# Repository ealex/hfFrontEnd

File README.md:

# hfFrontEnd
Receiver front end, to go along with https://github.com/ealex/hfBandPassFilterBlock

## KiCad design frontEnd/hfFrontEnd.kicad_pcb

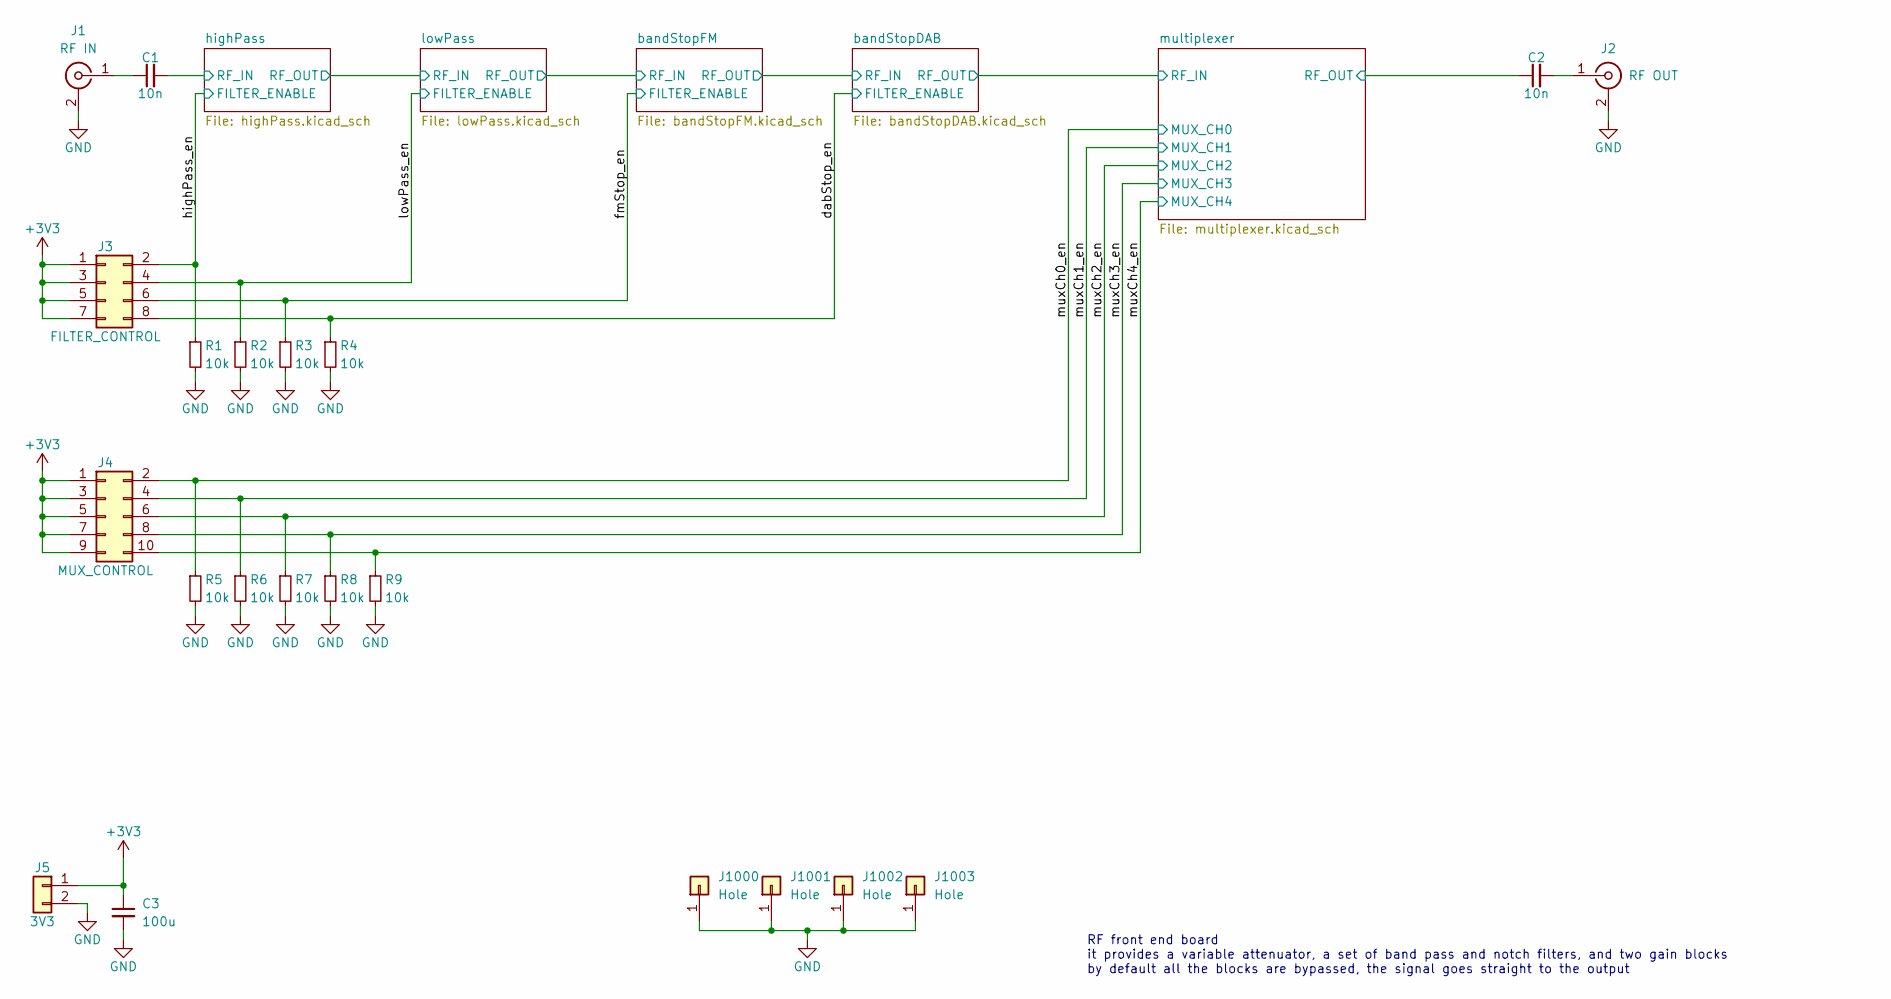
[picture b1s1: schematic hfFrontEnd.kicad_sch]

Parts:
C1, C2: 10n; C_0805_2012Metric
C3: 100u; CP_Radial_D5.0mm_P2.50mm
J1: RF IN; SMA
J2: RF OUT; SMA
J3: FILTER_CONTROL; PinHeader_2x04_P2.54mm_Vertical
J4: MUX_CONTROL; PinHeader_2x05_P2.54mm_Vertical
J5: 3V3; PinHeader_1x02_P2.54mm_Vertical
J1000, J1001, J1002, J1003: Hole; MountingHole_3.2mm_M3_DIN965_Pad
R1, R2, R3, R4, R5, R6, R7, R8, R9: 10k; R_0805_2012Metric

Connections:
+3V3: C3.1, J3.1, J3.3, J3.5, J3.7, J4.1, J4.3, J4.5, J4.7, J4.9, J5.1; also elsewhere on the board
/dabStop_en: J3.8, R4.1; also elsewhere on the board
/fmStop_en: J3.6, R3.1; also elsewhere on the board
/highPass/RF_IN: C1.2; also elsewhere on the board
/highPass_en: J3.2, R1.1; also elsewhere on the board
/lowPass_en: J3.4, R2.1; also elsewhere on the board
/multiplexer/RF_OUT: C2.1; also elsewhere on the board
/muxCh0_en: J4.2, R5.1; also elsewhere on the board
/muxCh1_en: J4.4, R6.1; also elsewhere on the board
/muxCh2_en: J4.6, R7.1; also elsewhere on the board
/muxCh3_en: J4.8, R8.1; also elsewhere on the board
/muxCh4_en: J4.10, R9.1; also elsewhere on the board
GND: C3.2, J1.2 (Ext), J2.2 (Ext), J5.2, J1000.1, J1001.1, J1002.1, J1003.1, R1.2, R2.2, R3.2, R4.2, R5.2, R6.2, R7.2, R8.2, R9.2; also elsewhere on the board
unnamed: C1.1, J1.1 (In)
unnamed: C2.2, J2.1 (In)

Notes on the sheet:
RF front end board it provides a variable attenuator, a set of band pass and notch filters, and two gain blocks by default all the blocks are bypassed, the signal goes straight to the output

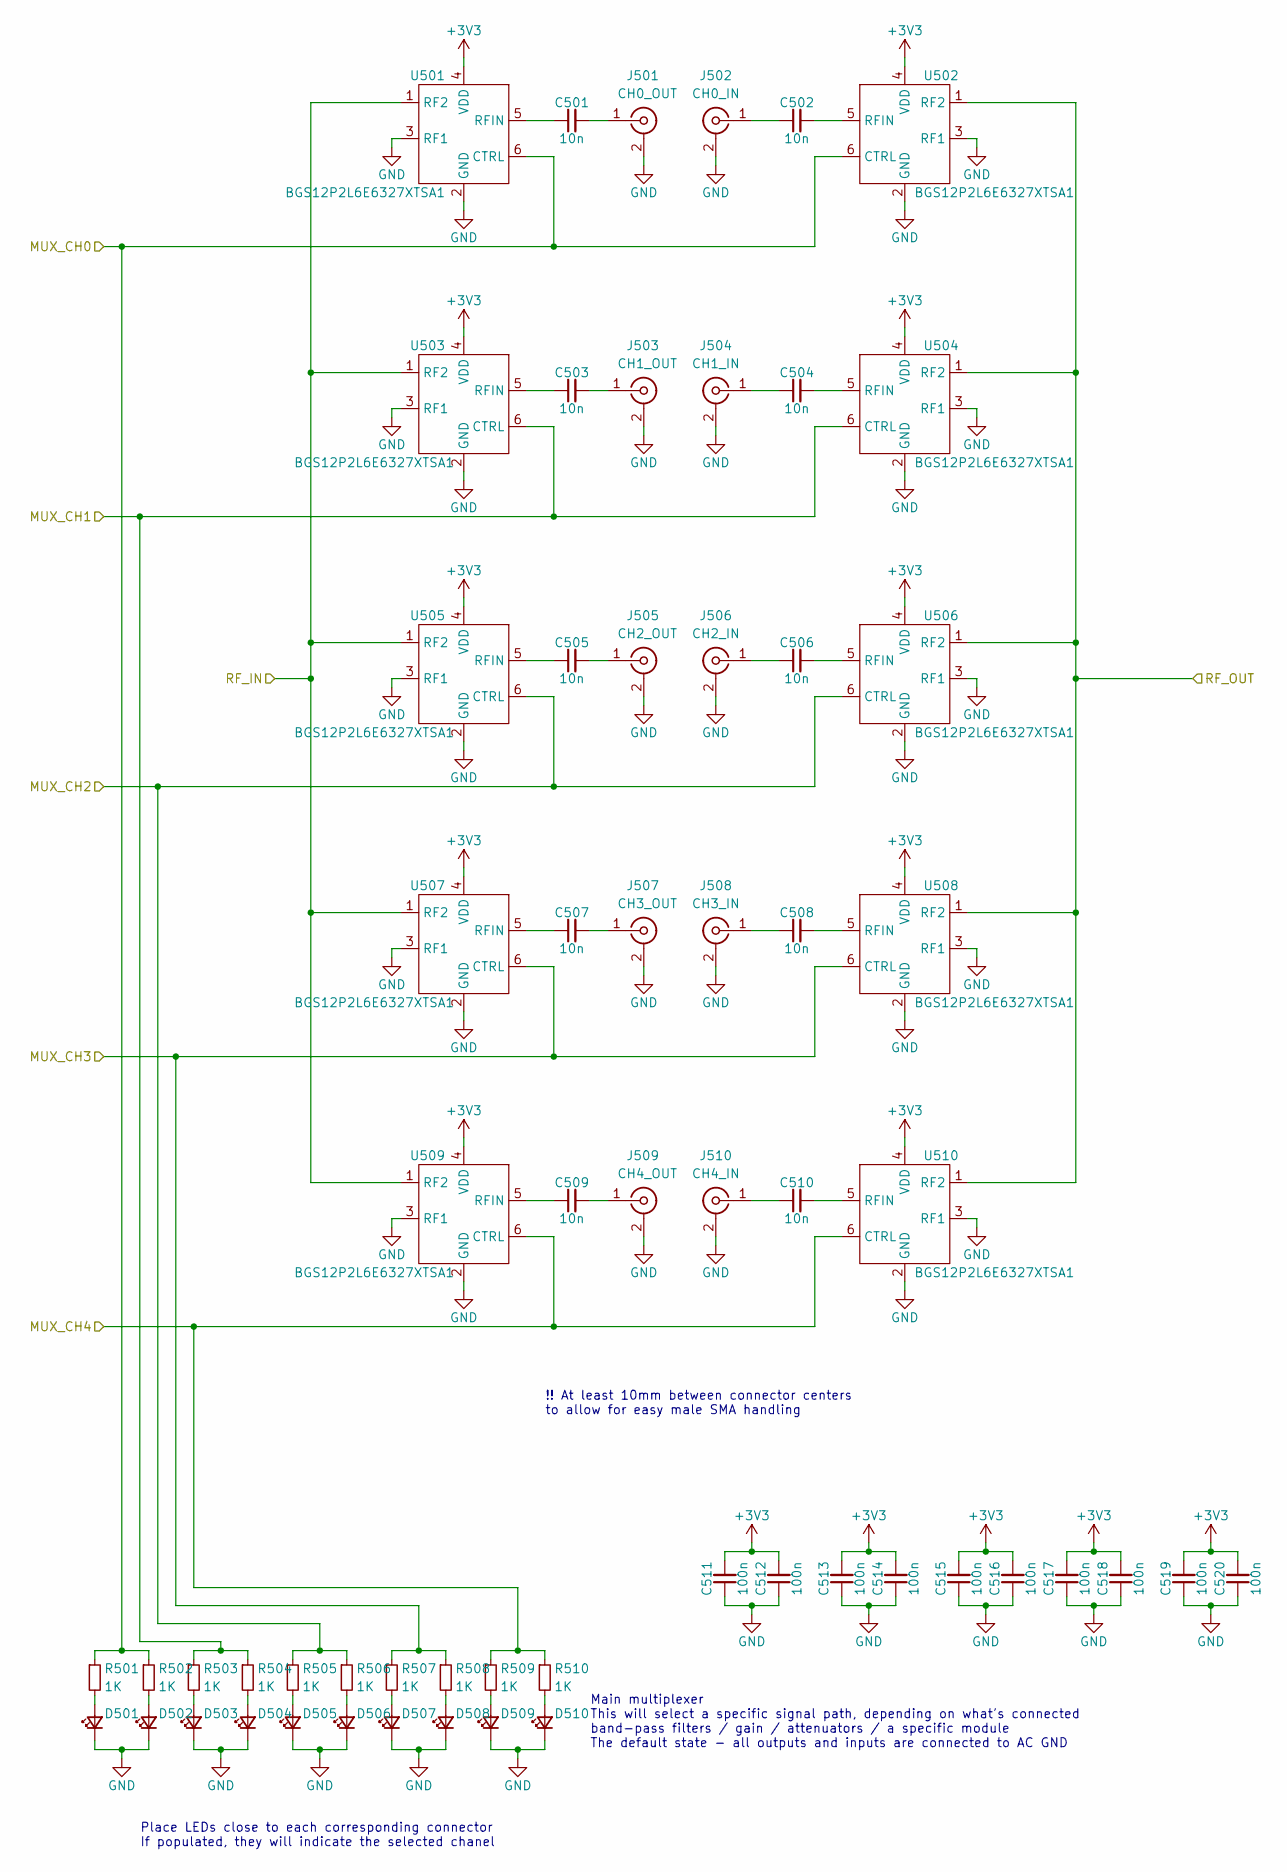
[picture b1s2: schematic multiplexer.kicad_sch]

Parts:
C501, C502, C503, C504, C505, C506, C507, C508, C509, C510: 10n; C_0805_2012Metric
C511, C512, C513, C514, C515, C516, C517, C518, C519, C520: 100n; C_0805_2012Metric
D501, D502, D503, D504, D505, D506, D507, D508, D509, D510: LED_Small; LED_0805_2012Metric
J501: CH0_OUT; SMA_FEM_TH_VERTICAL
J502: CH0_IN; SMA_FEM_TH_VERTICAL
J503: CH1_OUT; SMA_FEM_TH_VERTICAL
J504: CH1_IN; SMA_FEM_TH_VERTICAL
J505: CH2_OUT; SMA_FEM_TH_VERTICAL
J506: CH2_IN; SMA_FEM_TH_VERTICAL
J507: CH3_OUT; SMA_FEM_TH_VERTICAL
J508: CH3_IN; SMA_FEM_TH_VERTICAL
J509: CH4_OUT; SMA_FEM_TH_VERTICAL
J510: CH4_IN; SMA_FEM_TH_VERTICAL
R501, R502, R503, R504, R505, R506, R507, R508, R509, R510: 1K; R_0805_2012Metric
U501, U502, U503, U504, U505, U506, U507, U508, U509, U510: BGS12P2L6E6327XTSA1

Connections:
+3V3: C511.2, C512.2, C513.2, C514.2, C515.2, C516.2, C517.2, C518.2, C519.2, C520.2, U501.4 (VDD), U502.4 (VDD), U503.4 (VDD), U504.4 (VDD), U505.4 (VDD), U506.4 (VDD), U507.4 (VDD), U508.4 (VDD), U509.4 (VDD), U510.4 (VDD); also elsewhere on the board
/bandStopDAB/RF_OUT: U501.1 (RF2), U503.1 (RF2), U505.1 (RF2), U507.1 (RF2), U509.1 (RF2); also elsewhere on the board
/multiplexer/RF_OUT: U502.1 (RF2), U504.1 (RF2), U506.1 (RF2), U508.1 (RF2), U510.1 (RF2); also elsewhere on the board
/muxCh0_en: R501.1, R502.1, U501.6 (CTRL), U502.6 (CTRL); also elsewhere on the board
/muxCh1_en: R503.1, R504.1, U503.6 (CTRL), U504.6 (CTRL); also elsewhere on the board
/muxCh2_en: R505.1, R506.1, U505.6 (CTRL), U506.6 (CTRL); also elsewhere on the board
/muxCh3_en: R507.1, R508.1, U507.6 (CTRL), U508.6 (CTRL); also elsewhere on the board
/muxCh4_en: R509.1, R510.1, U509.6 (CTRL), U510.6 (CTRL); also elsewhere on the board
GND: C511.1, C512.1, C513.1, C514.1, C515.1, C516.1, C517.1, C518.1, C519.1, C520.1, D501.1 (K), D502.1 (K), D503.1 (K), D504.1 (K), D505.1 (K), D506.1 (K), D507.1 (K), D508.1 (K), D509.1 (K), D510.1 (K), J501.2 (Ext), J502.2 (Ext), J503.2 (Ext), J504.2 (Ext), J505.2 (Ext), J506.2 (Ext), J507.2 (Ext), J508.2 (Ext), J509.2 (Ext), J510.2 (Ext), U501.2 (GND), U501.3 (RF1), U502.2 (GND), U502.3 (RF1), U503.2 (GND), U503.3 (RF1), U504.2 (GND), U504.3 (RF1), U505.2 (GND), U505.3 (RF1), U506.2 (GND), U506.3 (RF1), U507.2 (GND), U507.3 (RF1), U508.2 (GND), U508.3 (RF1), U509.2 (GND), U509.3 (RF1), U510.2 (GND), U510.3 (RF1); also elsewhere on the board
unnamed: C501.1, U501.5 (RFIN)
unnamed: C501.2, J501.1 (In)
unnamed: C502.1, J502.1 (In)
unnamed: C502.2, U502.5 (RFIN)
unnamed: C503.1, U503.5 (RFIN)
unnamed: C503.2, J503.1 (In)
unnamed: C504.1, J504.1 (In)
unnamed: C504.2, U504.5 (RFIN)
unnamed: C505.1, U505.5 (RFIN)
unnamed: C505.2, J505.1 (In)
unnamed: C506.1, J506.1 (In)
unnamed: C506.2, U506.5 (RFIN)
unnamed: C507.1, U507.5 (RFIN)
unnamed: C507.2, J507.1 (In)
unnamed: C508.1, J508.1 (In)
unnamed: C508.2, U508.5 (RFIN)
unnamed: C509.1, U509.5 (RFIN)
unnamed: C509.2, J509.1 (In)
unnamed: C510.1, J510.1 (In)
unnamed: C510.2, U510.5 (RFIN)
unnamed: D501.2 (A), R501.2
unnamed: D502.2 (A), R502.2
unnamed: D503.2 (A), R503.2
unnamed: D504.2 (A), R504.2
unnamed: D505.2 (A), R505.2
unnamed: D506.2 (A), R506.2
unnamed: D507.2 (A), R507.2
unnamed: D508.2 (A), R508.2
unnamed: D509.2 (A), R509.2
unnamed: D510.2 (A), R510.2

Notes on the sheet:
!! At least 10mm between connector centers to allow for easy male SMA handling
Place LEDs close to each corresponding connector If populated, they will indicate the selected chanel
Main multiplexer This will select a specific signal path, depending on what's connected band-pass filters / gain / attenuators / a specific module The default state - all outputs and inputs are connected to AC GND

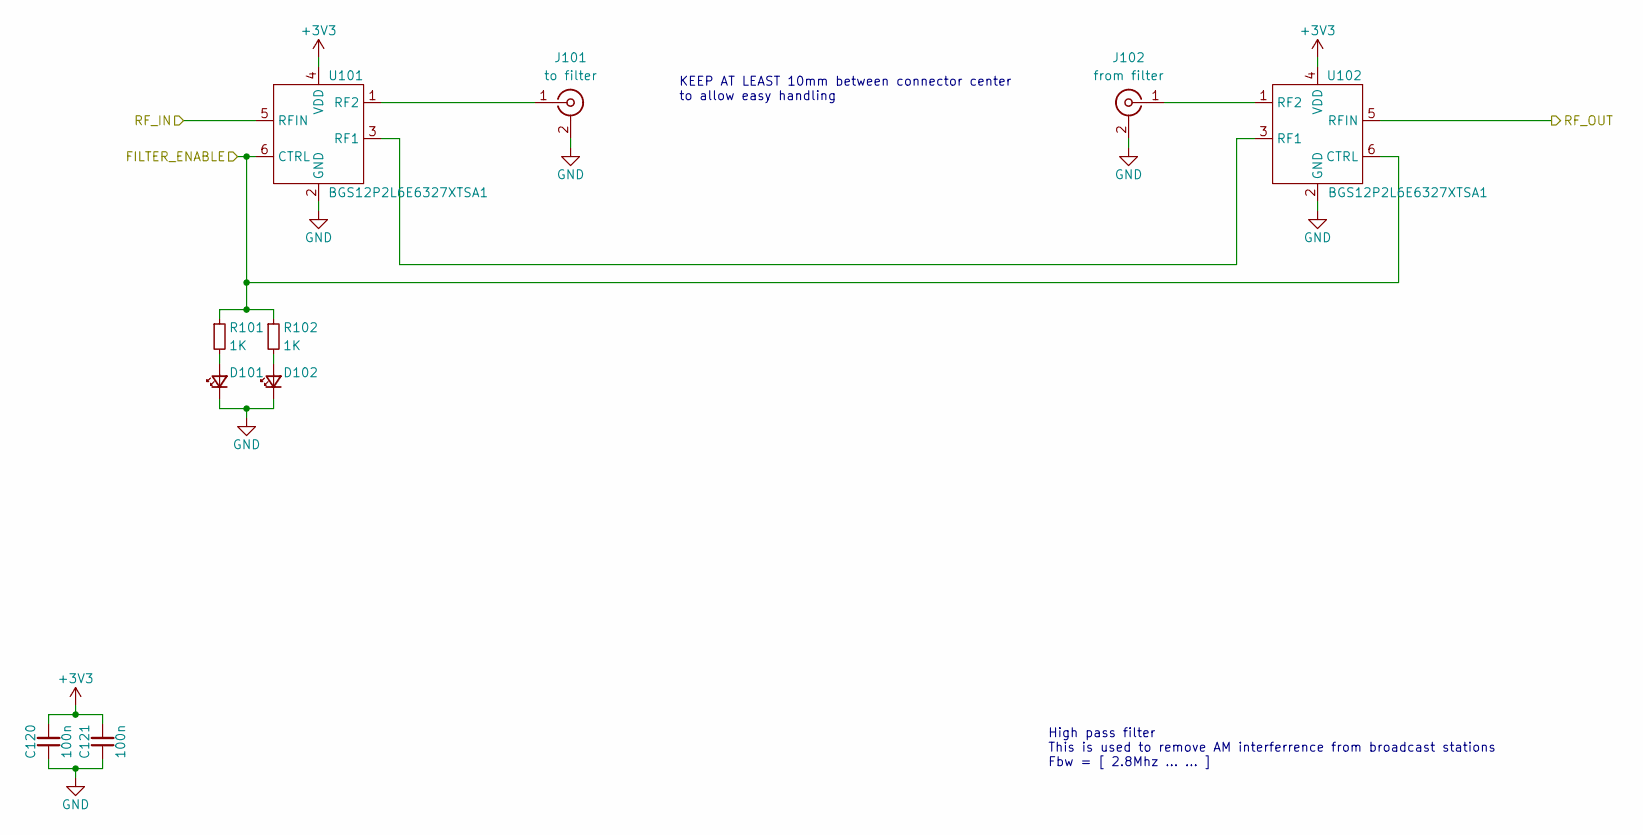
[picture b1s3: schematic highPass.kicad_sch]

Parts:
C120, C121: 100n; C_0805_2012Metric
D101, D102: LED_Small; LED_0805_2012Metric
J101: to filter; SMA_FEM_TH_VERTICAL
J102: from filter; SMA_FEM_TH_VERTICAL
R101, R102: 1K; R_0805_2012Metric
U101, U102: BGS12P2L6E6327XTSA1

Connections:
+3V3: C120.2, C121.2, U101.4 (VDD), U102.4 (VDD); also elsewhere on the board
/highPass/RF_IN: U101.5 (RFIN); also elsewhere on the board
/highPass/RF_OUT: U102.5 (RFIN); also elsewhere on the board
/highPass_en: R101.1, R102.1, U101.6 (CTRL), U102.6 (CTRL); also elsewhere on the board
GND: C120.1, C121.1, D101.1 (K), D102.1 (K), J101.2 (Ext), J102.2 (Ext), U101.2 (GND), U102.2 (GND); also elsewhere on the board
unnamed: D101.2 (A), R101.2
unnamed: D102.2 (A), R102.2
unnamed: J101.1 (In), U101.1 (RF2)
unnamed: J102.1 (In), U102.1 (RF2)
unnamed: U101.3 (RF1), U102.3 (RF1)

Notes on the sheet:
KEEP AT LEAST 10mm between connector center to allow easy handling
High pass filter This is used to remove AM interferrence from broadcast stations Fbw = [ 2.8Mhz ... ... ]

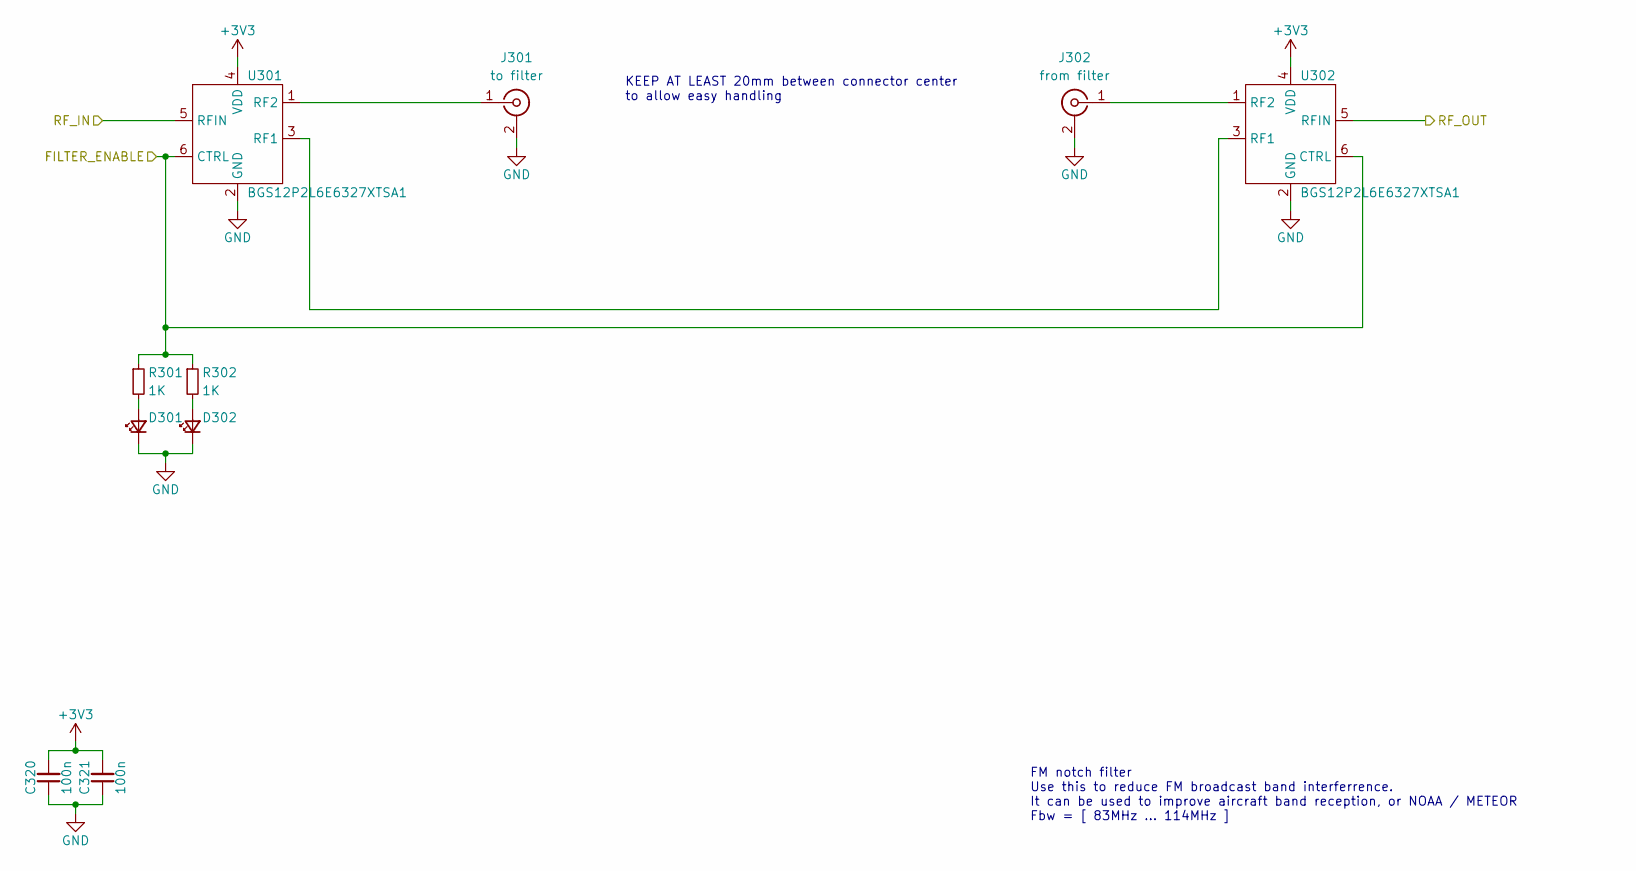
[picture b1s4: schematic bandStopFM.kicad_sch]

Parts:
C320, C321: 100n; C_0805_2012Metric
D301, D302: LED_Small; LED_0805_2012Metric
J301: to filter; SMA_FEM_TH_VERTICAL
J302: from filter; SMA_FEM_TH_VERTICAL
R301, R302: 1K; R_0805_2012Metric
U301, U302: BGS12P2L6E6327XTSA1

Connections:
+3V3: C320.2, C321.2, U301.4 (VDD), U302.4 (VDD); also elsewhere on the board
/bandStopDAB/RF_IN: U302.5 (RFIN); also elsewhere on the board
/bandStopFM/RF_IN: U301.5 (RFIN); also elsewhere on the board
/fmStop_en: R301.1, R302.1, U301.6 (CTRL), U302.6 (CTRL); also elsewhere on the board
GND: C320.1, C321.1, D301.1 (K), D302.1 (K), J301.2 (Ext), J302.2 (Ext), U301.2 (GND), U302.2 (GND); also elsewhere on the board
unnamed: D301.2 (A), R301.2
unnamed: D302.2 (A), R302.2
unnamed: J301.1 (In), U301.1 (RF2)
unnamed: J302.1 (In), U302.1 (RF2)
unnamed: U301.3 (RF1), U302.3 (RF1)

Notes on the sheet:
FM notch filter Use this to reduce FM broadcast band interferrence. It can be used to improve aircraft band reception, or NOAA / METEOR Fbw = [ 83MHz ... 114MHz ]
KEEP AT LEAST 20mm between connector center to allow easy handling

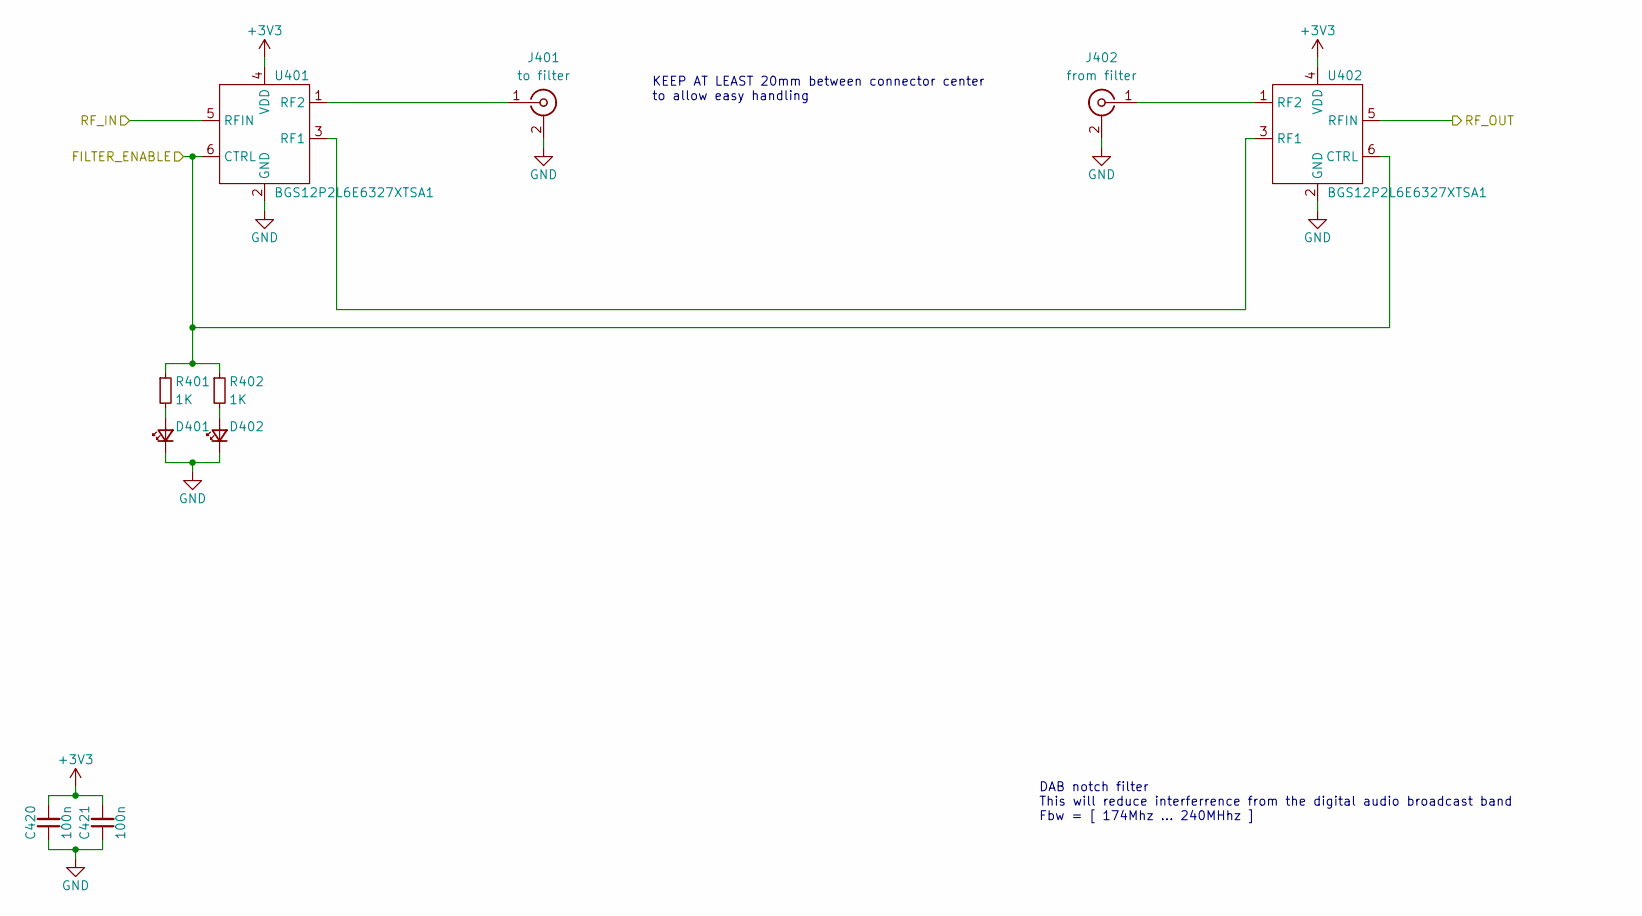
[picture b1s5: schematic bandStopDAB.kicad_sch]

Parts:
C420, C421: 100n; C_0805_2012Metric
D401, D402: LED_Small; LED_0805_2012Metric
J401: to filter; SMA_FEM_TH_VERTICAL
J402: from filter; SMA_FEM_TH_VERTICAL
R401, R402: 1K; R_0805_2012Metric
U401, U402: BGS12P2L6E6327XTSA1

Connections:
+3V3: C420.2, C421.2, U401.4 (VDD), U402.4 (VDD); also elsewhere on the board
/bandStopDAB/RF_IN: U401.5 (RFIN); also elsewhere on the board
/bandStopDAB/RF_OUT: U402.5 (RFIN); also elsewhere on the board
/dabStop_en: R401.1, R402.1, U401.6 (CTRL), U402.6 (CTRL); also elsewhere on the board
GND: C420.1, C421.1, D401.1 (K), D402.1 (K), J401.2 (Ext), J402.2 (Ext), U401.2 (GND), U402.2 (GND); also elsewhere on the board
unnamed: D401.2 (A), R401.2
unnamed: D402.2 (A), R402.2
unnamed: J401.1 (In), U401.1 (RF2)
unnamed: J402.1 (In), U402.1 (RF2)
unnamed: U401.3 (RF1), U402.3 (RF1)

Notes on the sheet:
DAB notch filter This will reduce interferrence from the digital audio broadcast band Fbw = [ 174Mhz ... 240MHhz ]
KEEP AT LEAST 20mm between connector center to allow easy handling

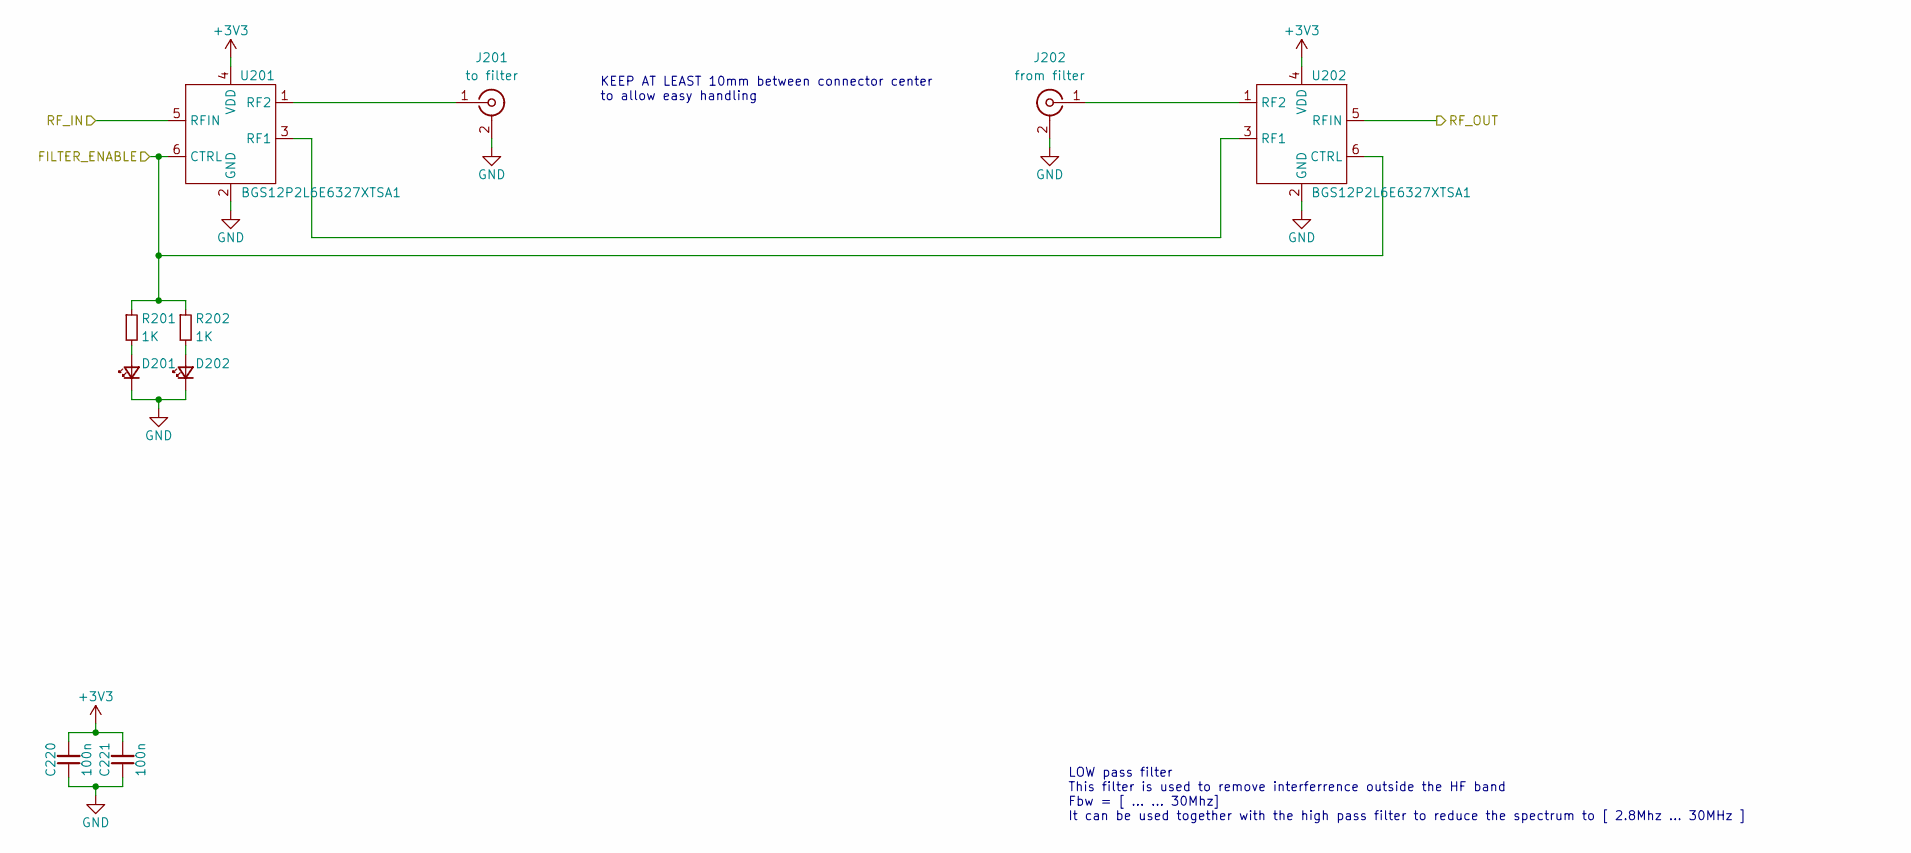
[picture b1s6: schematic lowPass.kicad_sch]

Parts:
C220, C221: 100n; C_0805_2012Metric
D201, D202: LED_Small; LED_0805_2012Metric
J201: to filter; SMA_FEM_TH_VERTICAL
J202: from filter; SMA_FEM_TH_VERTICAL
R201, R202: 1K; R_0805_2012Metric
U201, U202: BGS12P2L6E6327XTSA1

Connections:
+3V3: C220.2, C221.2, U201.4 (VDD), U202.4 (VDD); also elsewhere on the board
/bandStopFM/RF_IN: U202.5 (RFIN); also elsewhere on the board
/highPass/RF_OUT: U201.5 (RFIN); also elsewhere on the board
/lowPass_en: R201.1, R202.1, U201.6 (CTRL), U202.6 (CTRL); also elsewhere on the board
GND: C220.1, C221.1, D201.1 (K), D202.1 (K), J201.2 (Ext), J202.2 (Ext), U201.2 (GND), U202.2 (GND); also elsewhere on the board
unnamed: D201.2 (A), R201.2
unnamed: D202.2 (A), R202.2
unnamed: J201.1 (In), U201.1 (RF2)
unnamed: J202.1 (In), U202.1 (RF2)
unnamed: U201.3 (RF1), U202.3 (RF1)

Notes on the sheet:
KEEP AT LEAST 10mm between connector center to allow easy handling
LOW pass filter This filter is used to remove interferrence outside the HF band Fbw = [ ... ... 30Mhz] It can be used together with the high pass filter to reduce the spectrum to [ 2.8Mhz ... 30MHz ]

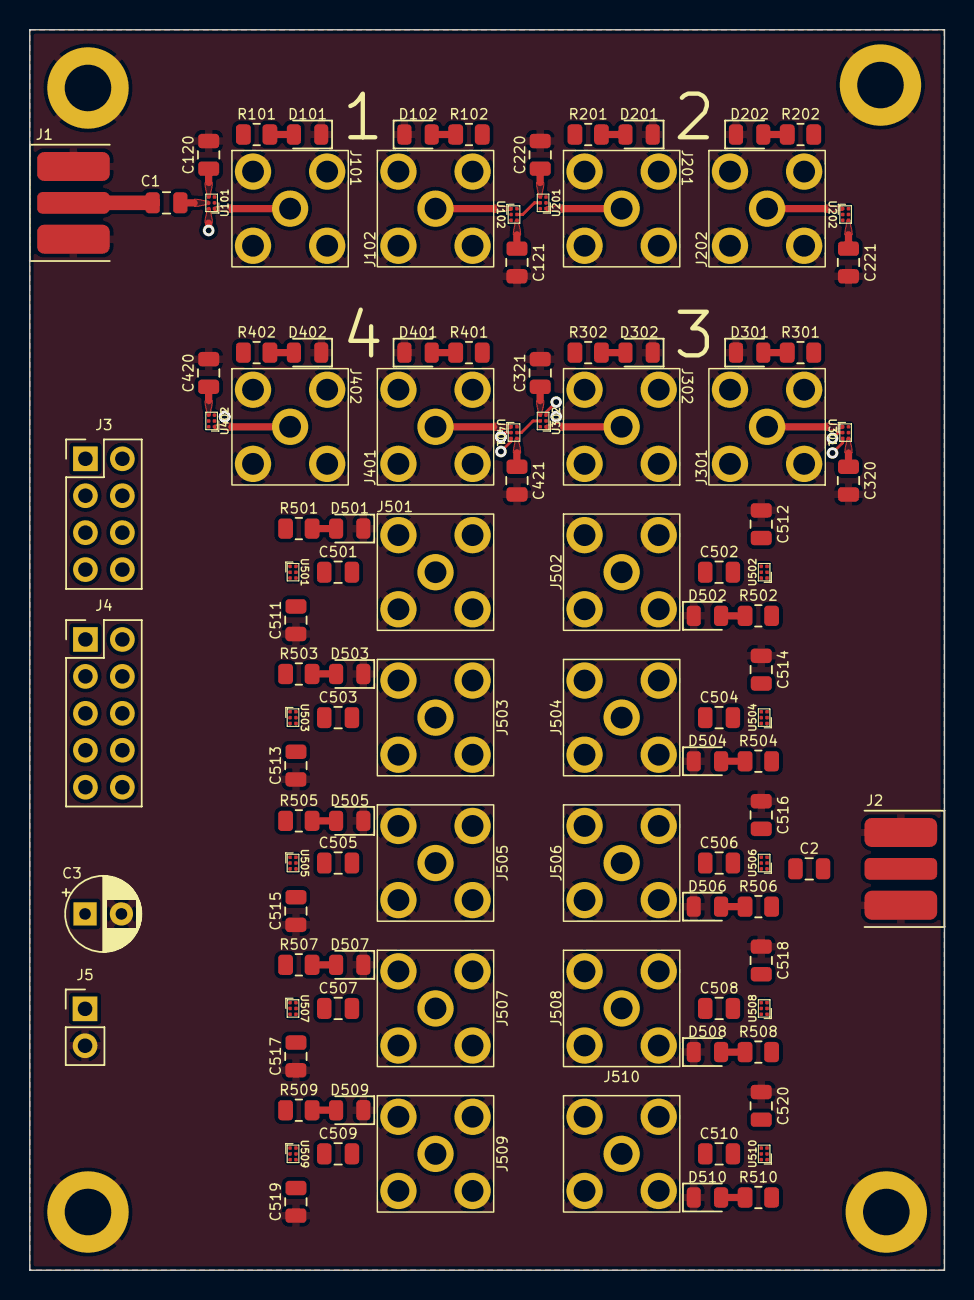
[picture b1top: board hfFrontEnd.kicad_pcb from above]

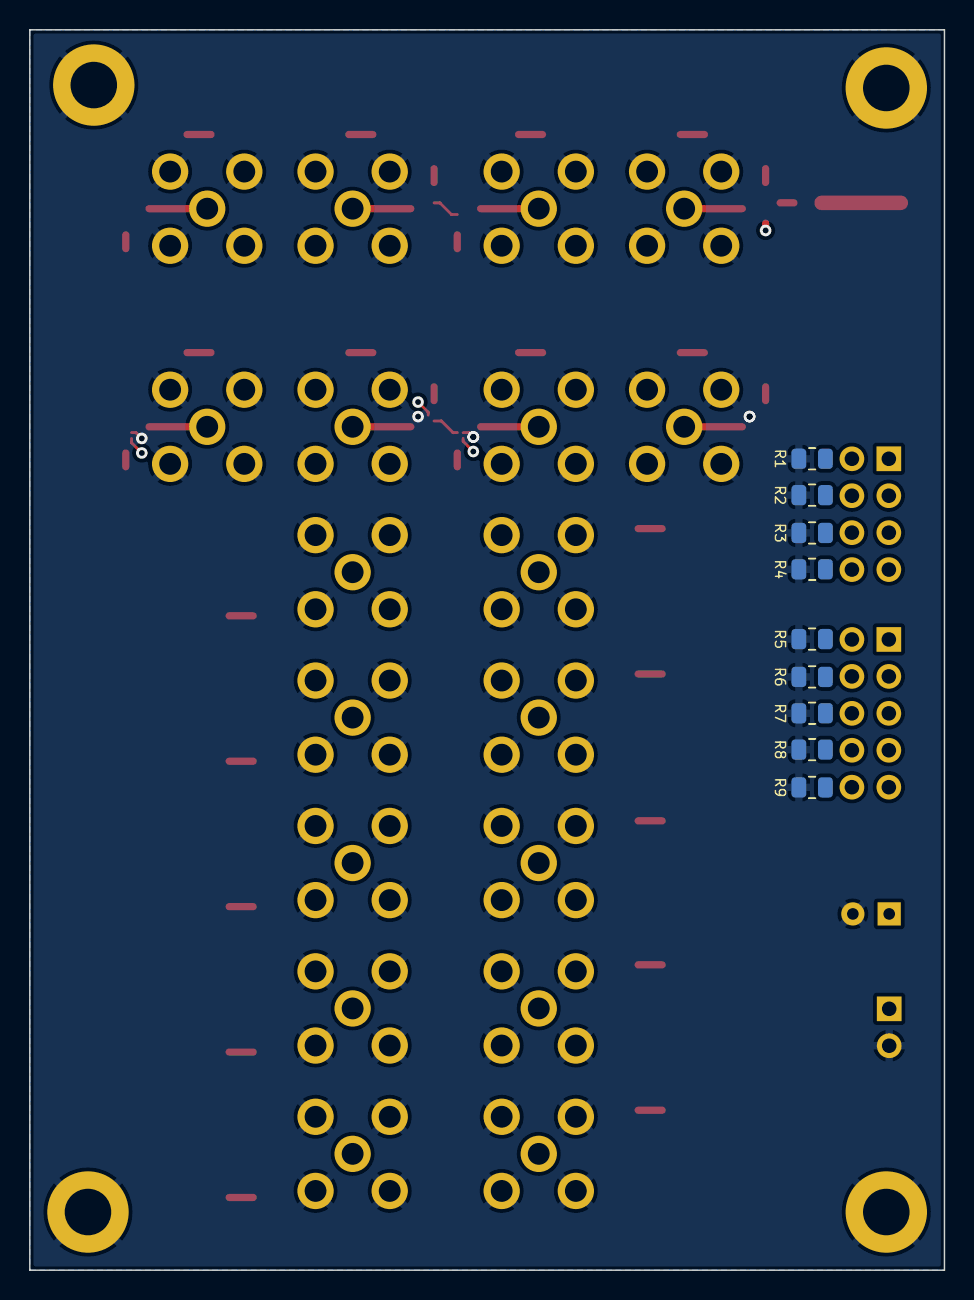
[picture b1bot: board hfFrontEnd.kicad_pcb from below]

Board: 4 copper layers, 62.9 x 85.3 mm, 121 parts (9 on the bottom side), 69 nets.

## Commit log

2023-09-01 add datasheets and documentation=
2023-09-01 start schematics
2023-09-01 update schematics, add bypass for the attenuator
2023-09-01 add pdf schematic
2023-09-01 simply schematic: remove attenuator and gain blocks; add 5 way multiplexer
2023-09-01 regenerate schematic PDF
2023-09-01 add leds for each filter block
2023-09-01 regenerate schematic
2023-09-01 assign footprints, part designators
2023-09-12 convert all embeded filter to plug-in modules, start pcb layout
